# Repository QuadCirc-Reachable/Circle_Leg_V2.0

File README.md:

# Circle_Leg_V2 — REACHABLE (QuadCirc) Full-Size Wheel-Leg Wheelchair Firmware

<p align="center">
  <b>English</b> | <a href="README_zh.md">中文</a>
</p>

<p align="center"><sub>The full-size prototype on display at HKUST ISD</sub></p>

Embedded control firmware for the **full-size REACHABLE (QuadCirc) electric wheelchair**. It has four
**CircLeg** eccentric wheel-leg modules. Each one rolls as an ordinary wheel on flat ground and turns
into a stepping leg to lift the chassis over the 5–18 cm curbs, thresholds and single steps that
wheelchair users meet every day. HKUST Final Year Design Project **SL05a-25** (2025–2026).

---

## Overview

Each CircLeg puts the wheel hub at an eccentric offset *r* inside a wheel of radius *R*. Rotating
the hub raises or lowers that corner of the chassis, and the wheel stays in contact with the ground
the whole time. With only **two motors per corner** (one wheel motor, one leg motor), the firmware:

- **Drives** like a normal wheelchair: skid-steer inverse kinematics for the trapezoidal chassis,
  four D-pad speed tiers, acceleration limits and smoothing.
- **Rides comfortably (COMFORT mode):** variable-impedance active suspension that maps a virtual
  Cartesian spring-damper to per-leg MIT gains, IMU body leveling, an online mass estimate, and
  **warp** (diagonal-twist) compensation that keeps all four wheels grounded.
- **Climbs steps (CLIMBING mode):** a per-leg state machine that detects step contact from the
  motor **torque residual** plus the wheel-speed drop, then follows a purely geometric climbing
  trajectory. The front pair climbs first and the back pair follows.
- **Stays safe:** host link-loss detection (500 ms), smooth mode transitions, singularity clamping,
  and live-tunable debug structs for SEGGER Ozone.

Related repositories:

| Repository | Content |
|------------|---------|
| **Circle_Leg_V2** (this repo) | Firmware for the full-size prototype (final deliverable), PCB and CAD |
| [Circle_Leg_V1.0](https://github.com/QuadCirc-Reachable/Circle_Leg_V1.0) | Firmware for the half-size proof-of-concept prototype |
| [Circle_Leg_Host_V2.0](https://github.com/QuadCirc-Reachable/Circle_Leg_Host_V2.0) | Host software: gamepad link + optional RealSense curb vision (Python package) |
| [Circle_Leg_Host_V1.0](https://github.com/QuadCirc-Reachable/Circle_Leg_Host_V1.0) | Previous single-script gamepad → UART bridge |

---

## Demo

<p align="center">
  
</p>

<p align="center">
  ▶ <a href="https://youtu.be/onJCvx1d8Sw">Watch the REACHABLE pitch video on YouTube</a>
</p>

---

## Key Results

Full-size prototype, as reported in the team's final project report (June 2026):

| Objective | Target | Demonstrated |
|-----------|--------|--------------|
| Basic locomotion | ≥ 1.2 m/s, differential steering | **1.49 m/s** operating (up to ≈ 2.2 m/s), emergency stop on link loss |
| CircLeg actuation | ±180° within 3 s | **≈ 0.8 s**, critically damped |
| Step climbing | 5–18 cm, seat pitch within ±15° | **5–18 cm**, seat pitch within **±5°** |
| Attitude & suspension | Level within ±10° on slopes | Chassis level within **±2–3°**; warp compensation operational |

> Measured with on-board telemetry (motor encoders, IMU, CAN-reported current) and debugger
> inspection, not with external instruments.

---

## System Architecture

```
┌──────────────────────────┐  UART 2 Mbit/s (CH343)   ┌──────────────────────────────────────────────┐
│ Host (Jetson Orin Nano)  │ ── PC_Msg @ 30 Hz ─────► │ STM32G473 · FreeRTOS                         │
│ Circle_Leg_Host_V2       │ ◄── Reachable_Msg ────── │                                              │
│ Xbox gamepad → frames    │                          │  PC_Comm (link watchdog 500 ms)              │
└──────────────────────────┘                          │     │                                        │
                                                      │     ▼                                        │
┌──────────────────────────┐        SPI               │  Chassis_Task  (500 Hz, 2 ms)                │
│ IMU  ICM-42688-P         │ ───────────────────────► │  ┌────────────────────────────────────────┐  │
└──────────────────────────┘                          │  │ Chassis state machine                  │  │
                                                      │  │ IDLE · ENERGY_SAVING · COMFORT · CLIMB │  │
                                                      │  ├────────────────────────────────────────┤  │
                                                      │  │ Impedance · GroundContact (warp) ·     │  │
                                                      │  │ Climbing FSM · Body PID · Inverse kin. │  │
                                                      │  └───────────────────┬────────────────────┘  │
                                                      │        Wheel_Leg ×4 (FL · FR · BL · BR)       │
                                                      └──────────┬─────────────────────┬─────────────┘
                                                        CAN 1 Mbit/s            CAN 1 Mbit/s
                                                                 ▼                     ▼
                                                  4× HT8115 wheel motors   4× DM J10010L-2EC leg motors
                                                  (MIT velocity mode)      (MIT impedance mode)
```

Every 2 ms the chassis task reads the latest gamepad command and the IMU attitude. It runs the
active mode's controllers, turns per-leg **height** targets into leg angles and MIT commands
`{θ, ω, Kp, Kd, τ_ff}`, sends one CAN frame per motor, and queues the telemetry for the host.

---

## Control Design

### Eccentric wheel-leg kinematics

With the hub offset *r* = 90 mm inside a wheel of radius *R* = 177.5 mm, the V2 firmware measures
the leg angle from the **lowest** pose (θ = 0°) to the **highest** pose (θ = 180°):

$$H(\theta) = R - r\cos\theta, \qquad \theta = \arccos\frac{R - H}{r}, \qquad \frac{\partial H}{\partial \theta} = r\sin\theta$$

The Jacobian vanishes at 0° and 180°, so every controller clamps the working range away from these
singularities.

### Chassis modes

| Mode | Wheels | Legs | Notes |
|------|--------|------|-------|
| **IDLE** | Stopped | Low-stiffness hold | Safe state; also entered on host link loss |
| **ENERGY_SAVING** | Joystick | Near 0° (lowest stance), stiff hold | Minimum power; ramps smoothly when leaving COMFORT |
| **COMFORT** | Joystick | Variable-impedance suspension + leveling + warp | Height presets on A/X/LB/RB/Y/B |
| **CLIMBING** | Joystick + auto advance | Per-leg climbing FSM | Front pair first, back pair follows |

`ML` / `MR` step backwards / forwards through IDLE → ENERGY_SAVING → COMFORT → CLIMBING. The
CALIBRATION, FREE_CONTROL and DEBUG states are compiled in but not in the live cycle. The DM leg
motors store their zero at the lowest pose in flash, so no calibration is needed at power-up.

### COMFORT — variable-impedance suspension

A virtual Cartesian spring-damper $(k_v, c_v)$ at each wheel contact point is mapped into joint
space through the eccentric Jacobian:

$$K_{p,i} = \left(\frac{\partial H}{\partial \theta_i}\right)^2 k_{v,i}, \qquad K_{d,i} = \left(\frac{\partial H}{\partial \theta_i}\right)^2 c_v, \qquad \tau_{ff,i} = \left(\frac{\hat M}{4} + m_\text{leg}\right) g \,\frac{\partial H}{\partial \theta_i} + \tau_{\text{warp},i}$$

- **Mass estimate** $\hat M$: low-pass-filtered sum of leg currents. It is frozen while the height
  target is slewing, so the unloading transient doesn't collapse the feed-forward.
- **Body leveling**: roll / pitch PID loops output per-leg height offsets. Gyro-rate damping and a
  load-adaptive gain scale keep the same tuning stable with or without a rider.
- **Warp**: see below. Overloaded diagonals get softer $k_v$ and underloaded ones are pushed down.

### Warp compensation

A rigid four-contact chassis has four height modes: heave, pitch, roll and **warp**. Pitch and roll
PID loops can't see warp, so on uneven floors one wheel can hang in the air. The firmware measures
warp directly from the diagonal current imbalance, with no extra sensor:

$$e_\text{warp} = \tfrac12\left(I_{FL} + I_{BR}\right) - \tfrac12\left(I_{FR} + I_{BL}\right)$$

It closes a dedicated loop on it: Kp / feed-forward modulation in COMFORT, and a PI loop on the
per-leg height offset in CLIMBING.

### CLIMBING — step-climbing pipeline

```
HOMING_IN ──► WAIT_START ──(X)──► PREP ──► DETECT ──► CLIMBING ──► COMPLETE ──► HOMING_OUT
 legs → 0°     hold at 0°          lift to    torque-residual  geometric    front pair done →
                                   165°, lean + wheel-drop     trajectory   nose-down lean,
                                   nose-up    score ≥ 1        (kinematic)  back pair repeats
```

- **Detection**: the torque residual $\tau_\text{res} = \tau_\text{fb} - \tau_\text{gravity}$ is tracked
  against an adaptive baseline and combined with a wheel-speed-drop score. Front and back legs have
  separate thresholds, and detection is inhibited while turning.
- **Trajectory**: the leg angle follows the geometry of a wheel rolling over the step edge, with
  step height *h* as a parameter. Auto chassis advance pushes the chassis through while the front
  wheels sit on the step.
- **Weight shift**: nose-up lean while the fronts climb. Afterwards a front-leg drop moves the CoM
  forward to unload the back wheels. Every offset is eased in and out with smoothstep ramps.
- Once both front legs are COMPLETE, pressing **X** again forces the back pair to climb, bypassing
  the detection gates, in case automatic detection doesn't fire.

The full design log, including every tuning decision behind the `dbg_ctrl` parameters, is in
[docs/UNIFIED_CONTROL_REFACTOR.md](docs/UNIFIED_CONTROL_REFACTOR.md).

### Locomotion

The trapezoidal chassis uses per-axle skid-steer gains so it tracks straight lines without drifting:

$$V_{FL/BL} = V_x - \omega_z k_{F/B}, \qquad V_{FR/BR} = V_x + \omega_z k_{F/B}, \qquad k_{F} = \frac{W_F}{W_\text{avg}},\; k_{B} = \frac{W_B}{W_\text{avg}}$$

A wheel-leg decoupling feed-forward cancels the wheel motion that hub rotation would otherwise cause,
so the chair doesn't lurch when the ride height changes.

---

## Repository Structure

```
Circle_Leg_V2/
├── Applications/                   # Application layer (this project)
│   ├── Chassis.hpp/.cpp            # Mode state machine, leveling, IK, climbing orchestration
│   ├── Chassis_Task.hpp/.cpp       # FreeRTOS 500 Hz control task
│   ├── Wheel_Leg.hpp/.cpp          # One CircLeg corner: height↔angle, MIT leg pipeline, wheel loop
│   ├── Impedance_Controller.*      # Variable-impedance suspension, mass estimate, warp modulation
│   ├── Ground_Contact.*            # Warp PI compensator
│   ├── Climbing_Dynamics.*         # Per-leg climbing FSM, step detection, trajectory
│   ├── Controller.*                # Joystick → (Vx, Wz), D-pad speed tiers, slew + LPF
│   ├── PC_Comm.*                   # Host UART link (RosComm framing), link watchdog
│   ├── Robot_Config.*              # Motor objects, CAN IDs, per-leg parameters
│   ├── Robot_Params.hpp            # Geometry, masses, IMU mounting, gains, limits
│   ├── Comm_Msg.hpp                # PC_Msg / Reachable_Msg layouts, button bitmasks
│   ├── Cust_Types.hpp, Helper.hpp  # Shared types and helpers
│   └── DM_Motor_Test.*             # Stand-alone DM J10010L bring-up test (USE_DM_MOTOR_TEST)
├── Core/                           # CubeMX HAL init + UserTask.cpp (task creation)
├── Drivers/, Middlewares/          # STM32G4 HAL, CMSIS, CMSIS-DSP (vendor)
├── RM2025-Core/                    # Submodule → private RM2025-Core (motors, CAN, IMU, RTOS)
├── hardware/
│   ├── power-distribution-board/   # KiCad 9 PCB: dual-battery 24 V power distribution
│   └── interface-cad/              # SolidWorks interface assembly and parts
├── docs/
│   ├── TECHNICAL_REPORT.md         # Control-system technical report (derivations)
│   ├── UNIFIED_CONTROL_REFACTOR.md # Climbing / leg-control design log
│   ├── CODE_STRUCTURE.txt          # Class map and control-flow notes
│   └── figures/
├── Makefile, Core.mk               # GNU Make build (arm-none-eabi-gcc)
├── RM2024-Template-G473.ioc        # STM32CubeMX project
├── stm32g473vetx_flash.ld          # Linker script
└── startup_stm32g473xx.s
```

---

## Getting Started

### Prerequisites

- `arm-none-eabi-gcc` (tested with GCC 12.2 from MSYS2) and GNU Make
- A SWD probe: SEGGER J-Link (Ozone / J-Flash) or ST-Link (STM32CubeProgrammer)
- Read access to the private
  [QuadCirc-Reachable/RM2025-Core](https://github.com/QuadCirc-Reachable/RM2025-Core) repository

> **RM2025-Core** is an internal library of the HKUST ENTERPRIZE RoboMaster team. It is linked as a
> git submodule pointing to a private repository and is **not** part of this repository's contents.

### Clone & build

```bash
git clone --recurse-submodules https://github.com/QuadCirc-Reachable/Circle_Leg_V2.0.git
cd Circle_Leg_V2.0
# already cloned without submodules?  git submodule update --init

make -j8
# → build/RM2024-Template-G473.elf / .hex / .bin
```

Every commit pins the exact RM2025-Core snapshot it was built with, so checking out any old commit
and running `git submodule update` rebuilds it byte-for-byte.

### Flash & debug

Flash `build/RM2024-Template-G473.elf` (or `.hex`) over SWD with Ozone, J-Flash or
STM32CubeProgrammer. For live tuning, open the ELF in SEGGER Ozone and watch or edit these globals:

| Global | Purpose |
|--------|---------|
| `dbg_ctrl` | Live-tunable climbing parameters (thresholds, pitch bias, ramps, speed ratios) |
| `DbgSummary` / `dbg_climb_plot` | Most useful signals for plotting at 500 Hz |
| `dbg_wheel_test_enable` / `dbg_wheel_test_rpm` | Wheel test bypass (`CHASSIS_DEBUG_SNAPSHOT`) |

### Configuration

| File | What to change |
|------|----------------|
| `Applications/Robot_Params.hpp` | Geometry, masses, IMU mounting / level trim, speed tiers, leveling gains, limits |
| `Applications/Robot_Config.cpp` | Motor IDs, CAN bus, direction flags |
| `Core/Inc/AppConfig.h` | RM2025-Core module switches (IMU, DM / HT motors, RosComm, `USE_DM_MOTOR_TEST`) |

---

## Operator Controls

Xbox gamepad on the host (see [Circle_Leg_Host_V2.0](https://github.com/QuadCirc-Reachable/Circle_Leg_Host_V2.0)):

| Input | Function |
|-------|----------|
| Left stick | Forward / backward speed |
| Right stick | Turn rate |
| `ML` / `MR` (View / Menu) | Previous / next chassis mode |
| D-pad ↓ ← → ↑ | Speed tier LOW 20 / MID_LOW 40 (default) / MID_HIGH 80 / HIGH 120 wheel RPM |
| `A` `X`/`LB` `RB` `Y` `B` | COMFORT ride-height presets: leg angle 45° / 90° / 135° / 145° / 165° |
| `X` in CLIMBING | Start the climb (WAIT_START → PREP); once the front pair is COMPLETE, press again to force the back pair |

---

## Communication Protocol

USART2 at **2 Mbit/s**, RosComm framing with CRC16:

```
| SOF 0xAA | len | ID 0xFF | CRC16(header) | payload (14 B) | CRC16(frame) |   → 21 bytes
```

`PC_Msg` (host → MCU, little-endian, packed):

| Field | Type | Range / meaning |
|-------|------|-----------------|
| `left_joystick.angle_x10_msg` | int16 | 0–3600 (deg × 10), −1 = released |
| `left_joystick.r_x1000_msg` | uint16 | 0–1000 (deflection) |
| `right_joystick.angle_x10_msg` | int16 | 0–3600, −1 = released |
| `right_joystick.r_x1000_msg` | uint16 | 0–1000 |
| `Left_trigger_x1000_msg` / `Right_trigger_x1000_msg` | uint16 | 0–1000 |
| `button_status` | uint8 | bit 0–7: LB, RB, X, A, B, Y, ML, MR |
| `dpad_status` | uint8 | bit 0–3: Up, Down, Left, Right |

`Reachable_Msg` (MCU → host, 40 bytes) reports each corner's leg position (deg × 10) and wheel RPM.
The field names still say GM6020 / M3508, left over from the half-size hardware.

Host V2.0 can also send RealSense curb-detection results (`0xFC`) and accept a vision-control
heartbeat (`0xFD`). This firmware consumes only the `0xFF` gamepad link. The MCU-side changes
needed to close the vision-in-the-loop climb are in Host V2.0's
[MCU integration guide](https://github.com/QuadCirc-Reachable/Circle_Leg_Host_V2.0/blob/main/docs/MCU_Integration_Guide.md).

---

## Hardware

<div align="center">
<table>
  <tr>
    <td align="center"><br><sub>Side view during development</sub></td>
    <td align="center"><br><sub>CircLeg modules, front view</sub></td>
  </tr>
</table>
</div>

| Item | Specification |
|------|---------------|
| MCU | STM32G473VET6, Cortex-M4F @ 170 MHz (ENTERPRIZE G4 control board) |
| RTOS | FreeRTOS, 1 kHz tick; chassis task 500 Hz |
| Wheel motors | 4× HT8115, MIT velocity mode |
| Leg motors | 4× DM J10010L-2EC, MIT impedance mode |
| Buses | 2× classic CAN @ 1 Mbit/s (FDCAN peripheral); USART2 @ 2 Mbit/s to host |
| IMU | ICM-42688-P (SPI) |
| Geometry | *R* = 177.5 mm, *r* = 90 mm; track 620 / 480 mm (front / back), wheelbase 385 mm |
| Mass | ≈ 39 kg vehicle |
| Power | 2× DJI TB48 (22.8 V); 24→19 V and 24→5 V converters |
| Host | Jetson Orin Nano + Intel RealSense D435 (curb perception) |

### Power distribution board

`hardware/power-distribution-board/` is a KiCad 9 project. Two battery inputs are OR-ed through
LM74700 ideal-diode controllers with BSC070N10NS5 MOSFETs, with TVS protection and a fuse. The
24 V rail is split to eight motor ports (four leg, four chassis), the mini PC, the control board and
a fan, using XT30 connectors. Custom footprints are in `Library.pretty/`. Jason Chan helped
develop this board.

### Interface CAD

`hardware/interface-cad/` holds the SolidWorks assembly `Assem3.SLDASM` and its parts.

---

## Documentation

| Document | Content |
|----------|---------|
| [docs/TECHNICAL_REPORT.md](docs/TECHNICAL_REPORT.md) | Control-system report: kinematics, leveling, impedance, warp, climbing, RTOS |
| [docs/UNIFIED_CONTROL_REFACTOR.md](docs/UNIFIED_CONTROL_REFACTOR.md) | Climbing pipeline and leg-control design log, with tuning history |
| [docs/CODE_STRUCTURE.txt](docs/CODE_STRUCTURE.txt) | Class hierarchy, per-mode control flow, key formulas |

---

## Team

**REACHABLE (QuadCirc)**, HKUST Final Year Design Project SL05a-25:

- **LIU Hualin** — embedded control lead: motor and MCU selection, dual-CAN hardware, and all of the firmware and control algorithms in this repository
- **FANG Ruoyun** — perception (RealSense curb detection) and HMI
- **WU Ziyao** — mechanical architecture, host–MCU communication
- **XU Jusen** — mechanical lead (CircLeg bracket, chassis, DFM/DFA)

Supervisors: Prof. Chi-Ying TSUI and Prof. Winnie Suk Wai LEUNG; co-supervisor Prof. SHI Ling.

---

## License

The application code in this repository is released under the [MIT License](LICENSE).
Third-party components keep their own licenses: STM32 HAL / CMSIS in `Drivers/` and `Middlewares/`,
and template files (`Core.mk`, `Core/Src/UserTask.cpp`) from the ENTERPRIZE RoboMaster team.
The `RM2025-Core` submodule is private and not covered by this license.

## Acknowledgments

- HKUST ENTERPRIZE RoboMaster team for RM2025-Core and the G4 project template
- Jason GAN (RM2024) for the original HT8115 motor driver
- Jason Chan for helping develop the power distribution board
- STMicroelectronics (HAL, CMSIS) and the FreeRTOS project
- Our friends and classmates at HKUST ISD

<p align="center"><sub>With our friends from HKUST ISD</sub></p>

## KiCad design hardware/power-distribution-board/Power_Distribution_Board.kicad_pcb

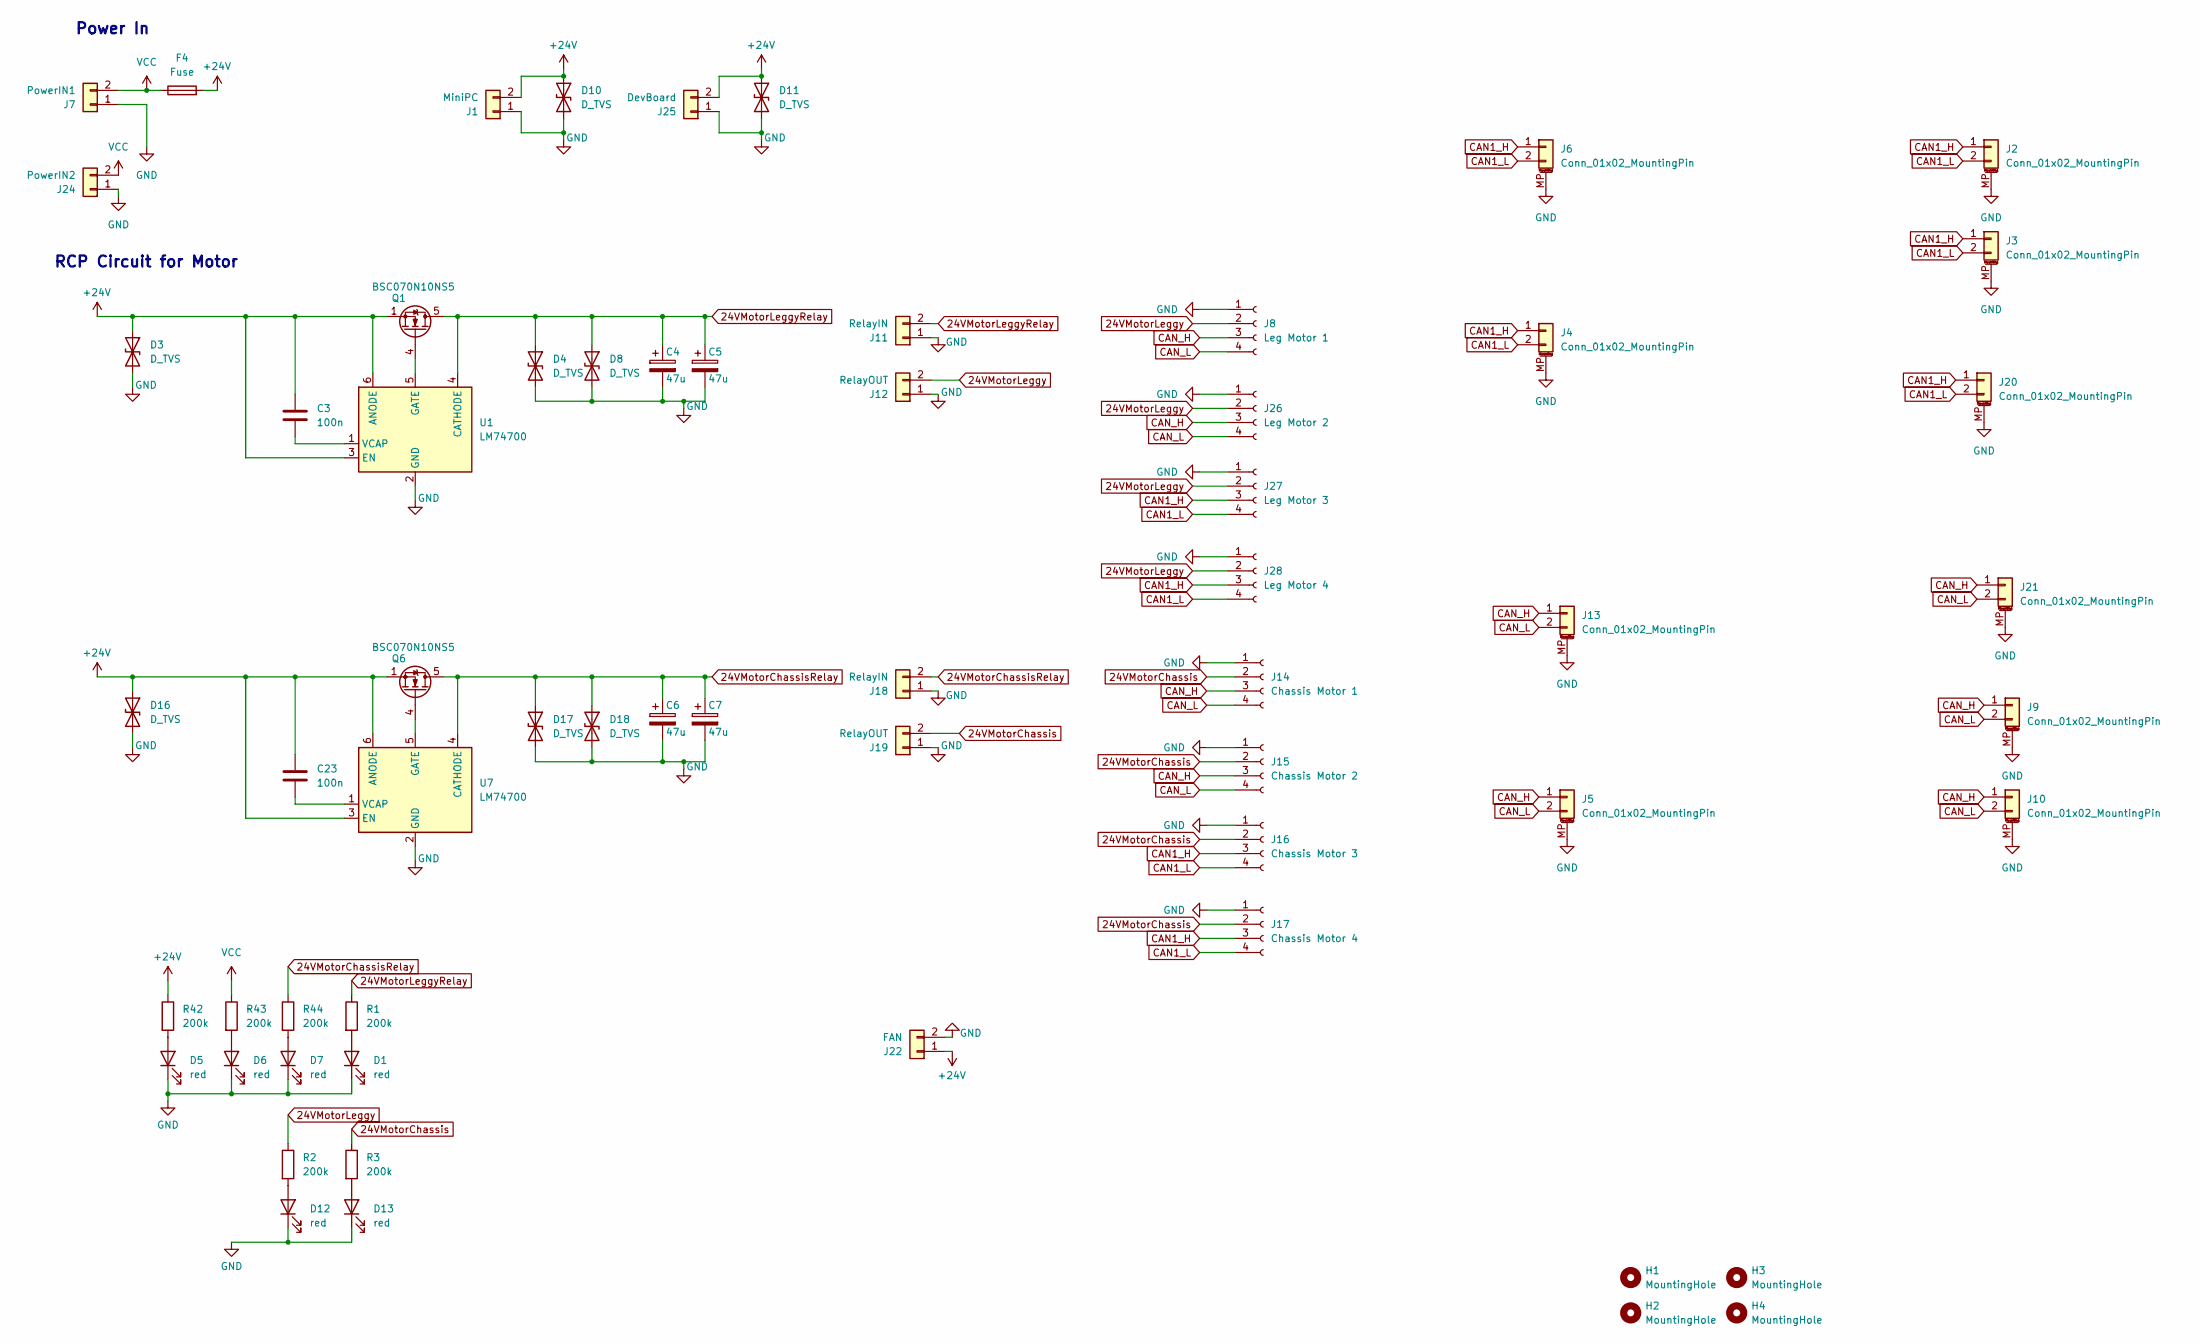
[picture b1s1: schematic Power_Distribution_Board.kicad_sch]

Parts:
C3, C23: 100n; C_0603_1608Metric; LCSC C14663
C4, C5, C6, C7: 47u; CP_Radial_D16.0mm_P7.50mm
D1, D5, D6, D7, D12, D13: red; LED_0603_1608Metric; LCSC C84256
D3, D4, D8, D10, D11, D16, D17, D18: D_TVS; D_SMC
F4: Fuse; FuseHolderSMD9.7x5mm
H1, H2, H3, H4: MountingHole; MountingHole_3.2mm_M3_Pad_Via
J1: MiniPC; AMASS_XT30U-M_1x02_P5.0mm_Vertical
J2, J3, J4, J5, J6, J9, J10, J13, J20, J21: Conn_01x02_MountingPin; JST_GH_BM02B-GHS-TBT_1x02-1MP_P1.25mm_Vertical
J7: PowerIN1; AMASS_XT60-F_1x02_P7.20mm_Vertical
J8: Leg Motor 1; AMASS_XT30_2+2_1x02_P5.0mm_Vertical
J11, J18: RelayIN; AMASS_XT60-F_1x02_P7.20mm_Vertical
J12, J19: RelayOUT; AMASS_XT60-F_1x02_P7.20mm_Vertical
J14: Chassis Motor 1; AMASS_XT30_2+2_1x02_P5.0mm_Vertical
J15: Chassis Motor 2; AMASS_XT30_2+2_1x02_P5.0mm_Vertical
J16: Chassis Motor 3; AMASS_XT30_2+2_1x02_P5.0mm_Vertical
J17: Chassis Motor 4; AMASS_XT30_2+2_1x02_P5.0mm_Vertical
J22: FAN; JST_XH_B2B-XH-A_1x02_P2.50mm_Vertical
J24: PowerIN2; AMASS_XT60-F_1x02_P7.20mm_Vertical
J25: DevBoard; AMASS_XT30U-M_1x02_P5.0mm_Vertical
J26: Leg Motor 2; AMASS_XT30_2+2_1x02_P5.0mm_Vertical
J27: Leg Motor 3; AMASS_XT30_2+2_1x02_P5.0mm_Vertical
J28: Leg Motor 4; AMASS_XT30_2+2_1x02_P5.0mm_Vertical
Q1, Q6: BSC070N10NS5; TDSON-8-1
R1, R2, R3, R42, R43, R44: 200k; R_0603_1608Metric; LCSC C23186
U1, U7: LM74700; SOT-23-6

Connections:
24VMotorChassis: J14.2, J15.2, J16.2, J17.2, J19.2, R3.1
24VMotorChassisRelay: C6.1, C7.1, D17.1 (A1), D18.1 (A1), J18.2, Q6.5 (D), R44.1, U7.4 (CATHODE)
24VMotorLeggy: J8.2, J12.2, J26.2, J27.2, J28.2, R2.1
24VMotorLeggyRelay: C4.1, C5.1, D4.1 (A1), D8.1 (A1), J11.2, Q1.5 (D), R1.1, U1.4 (CATHODE)
+24V: C3.1, C23.1, D3.1 (A1), D10.1 (A1), D11.1 (A1), D16.1 (A1), F4.2, J1.2, J22.1, J25.2, Q1.1 (S), Q1.2 (S), Q1.3 (S), Q6.1 (S), Q6.2 (S), Q6.3 (S), R42.1, U1.3 (EN), U1.6 (ANODE), U7.3 (EN), U7.6 (ANODE)
CAN1_H: J2.1, J3.1, J4.1, J6.1, J16.3, J17.3, J20.1, J27.3, J28.3
CAN1_L: J2.2, J3.2, J4.2, J6.2, J16.4, J17.4, J20.2, J27.4, J28.4
CAN_H: J5.1, J8.3, J9.1, J10.1, J13.1, J14.3, J15.3, J21.1, J26.3
CAN_L: J5.2, J8.4, J9.2, J10.2, J13.2, J14.4, J15.4, J21.2, J26.4
GND: C4.2, C5.2, C6.2, C7.2, D1.1 (K), D3.2 (A2), D4.2 (A2), D5.1 (K), D6.1 (K), D7.1 (K), D8.2 (A2), D10.2 (A2), D11.2 (A2), D12.1 (K), D13.1 (K), D16.2 (A2), D17.2 (A2), D18.2 (A2), J1.1, J2.MP (MountPin), J3.MP (MountPin), J4.MP (MountPin), J5.MP (MountPin), J6.MP (MountPin), J7.1, J8.1, J9.MP (MountPin), J10.MP (MountPin), J11.1, J12.1, J13.MP (MountPin), J14.1, J15.1, J16.1, J17.1, J18.1, J19.1, J20.MP (MountPin), J21.MP (MountPin), J22.2, J24.1, J25.1, J26.1, J27.1, J28.1, U1.2 (GND), U7.2 (GND)
unnamed: D1.2 (A), R1.2
unnamed: D5.2 (A), R42.2
unnamed: D6.2 (A), R43.2
unnamed: D7.2 (A), R44.2
unnamed: D12.2 (A), R2.2
unnamed: D13.2 (A), R3.2
unnamed: Q1.4 (G), U1.5 (GATE)
unnamed: Q6.4 (G), U7.5 (GATE)
unnamed: C3.2, U1.1 (VCAP)
unnamed: C23.2, U7.1 (VCAP)
VCC: F4.1, J7.2, J24.2, R43.1

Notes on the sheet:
RCP Circuit for Motor
Power In

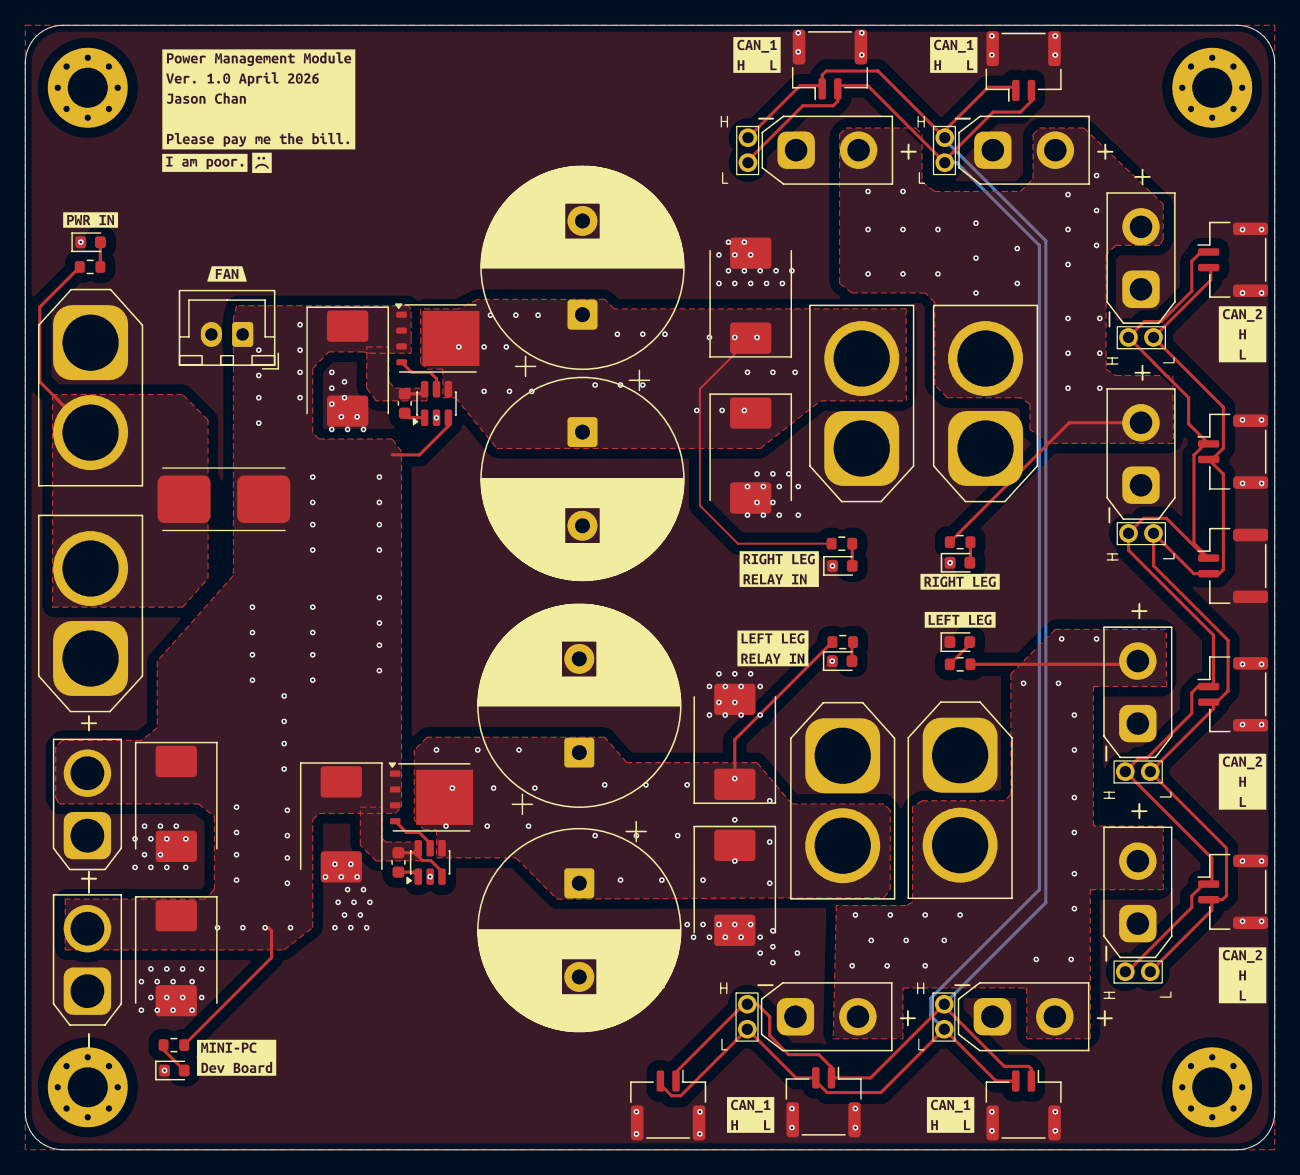
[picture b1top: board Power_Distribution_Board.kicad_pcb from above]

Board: 4 copper layers, 100.0 x 90.0 mm, 79 parts (0 on the bottom side), 21 nets.

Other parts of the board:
kibuzzard-69E79C0F: G***; kibuzzard-69E79C0F
kibuzzard-69E79C2E: G***; kibuzzard-69E79C2E
kibuzzard-69E79C27: G***; kibuzzard-69E79C27
kibuzzard-69E797B3: G***; kibuzzard-69E797B3
kibuzzard-69E797CC: G***; kibuzzard-69E797CC
kibuzzard-69E798A9, kibuzzard-69E798A9#2, kibuzzard-69E798A9#3: G***; kibuzzard-69E798A9
kibuzzard-69E7980C: G***; kibuzzard-69E7980C
kibuzzard-69E7988C, kibuzzard-69E7988C#2, kibuzzard-69E7988C#3, kibuzzard-69E7988C#4: G***; kibuzzard-69E7988C
kibuzzard-69E79826: G***; kibuzzard-69E79826
kibuzzard-69E79832: G***; kibuzzard-69E79832
kibuzzard-69E79866: G***; kibuzzard-69E79866
kibuzzard-69E87184: G***; kibuzzard-69E87184

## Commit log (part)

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2026-05-08 init
2026-05-12 V1, comfort mode checkpoint
2026-05-12 v1,comfort mode checkpoint 2
2026-05-12 fix comfort to ES falling issue
2026-05-22 update comfort mode transformation
2026-05-29 backup: project state before wired-control feature
    Snapshot of the unified leg-control refactor WIP (Chassis / Climbing_Dynamics /
    Impedance_Controller / Wheel_Leg + UNIFIED_CONTROL_REFACTOR.md design log) before
    starting the wired-control (hall joystick + 3 buttons) feature.

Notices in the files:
README.md:
License: MIT
